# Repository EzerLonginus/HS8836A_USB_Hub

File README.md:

# HS8836A_USB_Hub
Simple usb 2.0 hub using the HS8836A.  There are two designs, one is designed specifically for mounting directly to the side of my laptop, the other is with USB-C or USB Mini connectors and probably the one you'll want to actually look at..  
This schematic is identical to [Stefan Wagner](https://github.com/wagiminator) schematic at [OSHW Lab](https://oshwlab.com/wagiminator/hs8836-usb-2-0-hub_copy)

## Purpose
Originally, and more importantly for me, I wanted to design a slim-ish USB hub that I could connect to the side of my computer, without a cable dangling from it.  The design also needed to allow for airflow from the fans that are next to the USB port on my computer, and not to obstruct the other ports on the other side of the USB.  That being said, I created an addtional design to be a little more universally applicable for others (and myself later).  So likely you'll want to use the [HSS8836_USBC_Hub](hardware/HS8836A_USBC_hub) files instead of the older ones.  The older files are still available, although it's probably not really needed for anyone besides me.

## Scematic

## Layout

## To Do
* Post pictures of the old USB hub
* Populate and Test USBC Hub when boards arrive
* Post pictures of USBC board

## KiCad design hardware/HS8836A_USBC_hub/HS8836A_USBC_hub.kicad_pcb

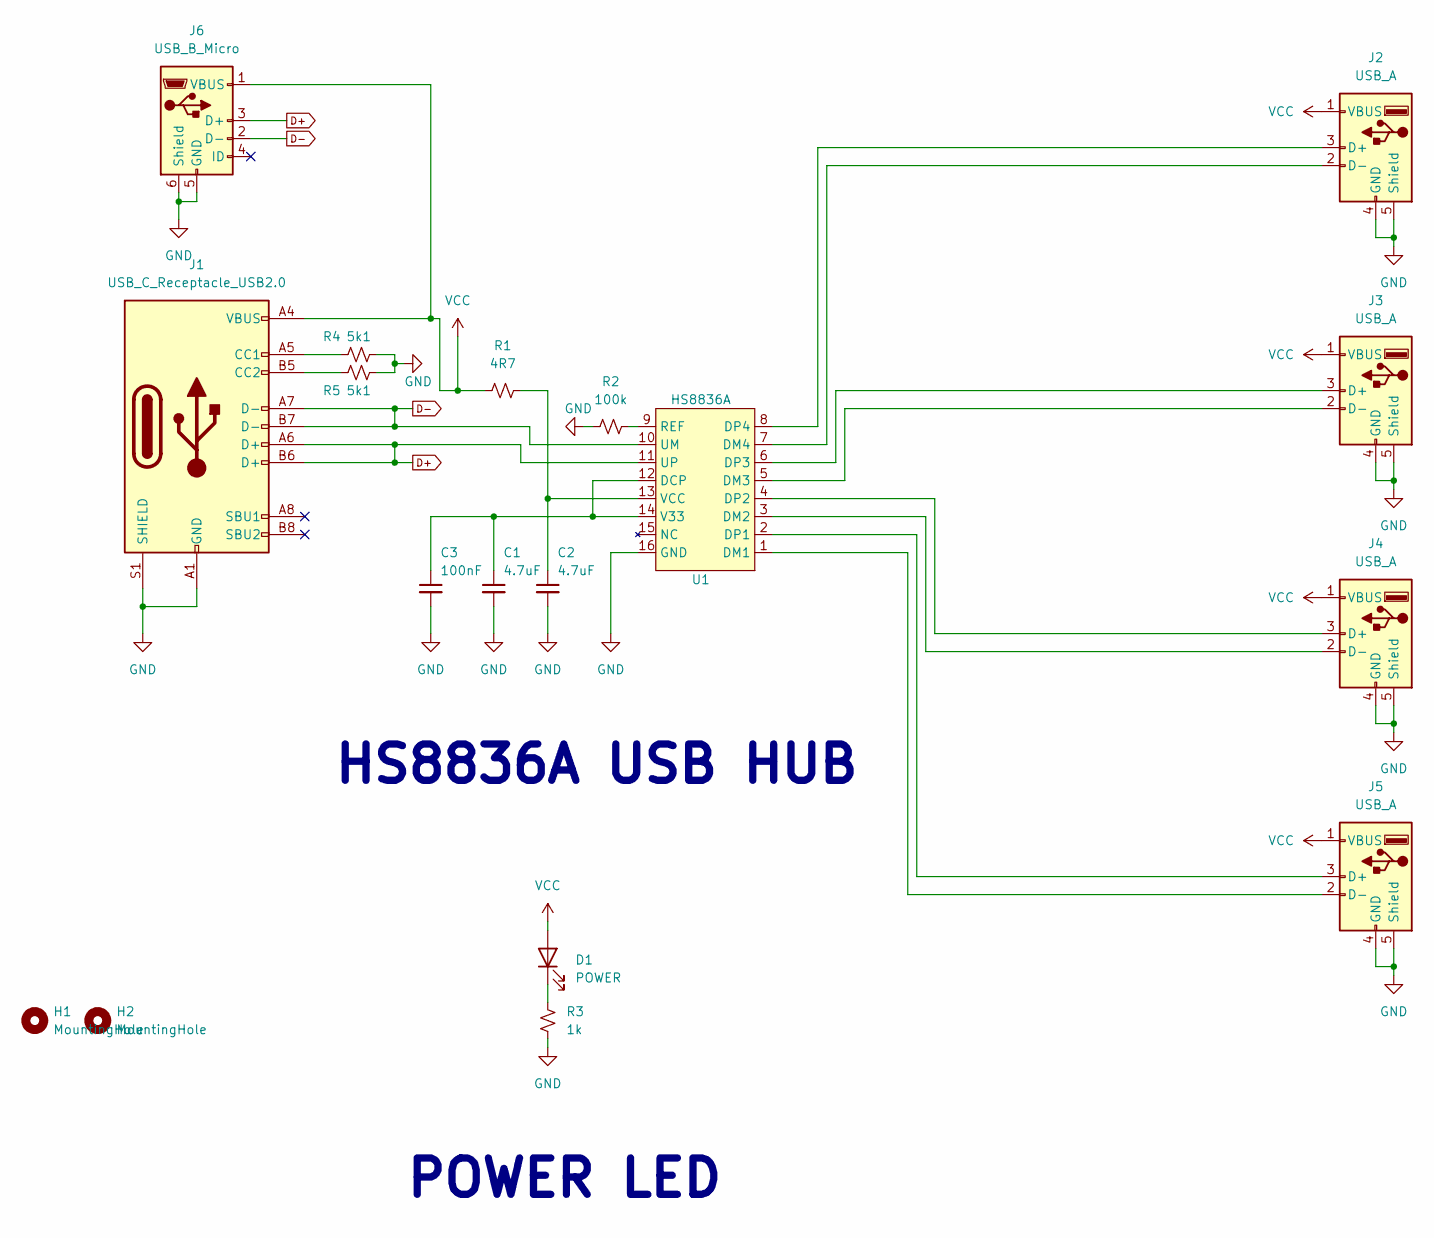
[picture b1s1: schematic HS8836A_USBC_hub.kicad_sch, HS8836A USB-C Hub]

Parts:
C1, C2: 4.7uF; C_0603_1608Metric_Pad1.08x0.95mm_HandSolder
C3: 100nF; C_0603_1608Metric_Pad1.08x0.95mm_HandSolder
D1: POWER; LED_1206_3216Metric
H1, H2: MountingHole; MountingHole_2.2mm_M2
J1: USB_C_Receptacle_USB2.0; USB_C_Receptacle_HRO_TYPE-C-31-M-12
J2, J3, J4, J5: USB_A; USB_A_Molex_67643_Horizontal
J6: USB_B_Micro; USB_Micro-B_Amphenol_10118193-0001LF_Horizontal
R1: 4R7; R_0603_1608Metric_Pad0.98x0.95mm_HandSolder
R2: 100k; R_0603_1608Metric_Pad0.98x0.95mm_HandSolder
R3: 1k; R_0603_1608Metric_Pad0.98x0.95mm_HandSolder
R4, R5: 5k1; R_0603_1608Metric_Pad0.98x0.95mm_HandSolder
U1: HS8836A; SOP-16_4.4x10.4mm_P1.27mm

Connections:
D+: J1.A6 (D+), J1.B6 (D+), J6.3 (D+), U1.11 (UP)
D-: J1.A7 (D-), J1.B7 (D-), J6.2 (D-), U1.10 (UM)
GND: C1.2, C2.2, C3.2, J1.A1 (GND), J1.A12 (GND), J1.B1 (GND), J1.B12 (GND), J1.S1 (SHIELD), J2.4 (GND), J2.5 (Shield), J3.4 (GND), J3.5 (Shield), J4.4 (GND), J4.5 (Shield), J5.4 (GND), J5.5 (Shield), J6.5 (GND), J6.6 (Shield), R2.1, R3.1, R4.2, R5.2, U1.16 (GND)
unnamed: D1.1 (K), R3.2
unnamed: J1.A5 (CC1), R4.1
unnamed: J1.B5 (CC2), R5.1
unnamed: J2.3 (D+), U1.8 (DP4)
unnamed: J2.2 (D-), U1.7 (DM4)
unnamed: J3.3 (D+), U1.6 (DP3)
unnamed: J3.2 (D-), U1.5 (DM3)
unnamed: J4.3 (D+), U1.4 (DP2)
unnamed: J4.2 (D-), U1.3 (DM2)
unnamed: J5.3 (D+), U1.2 (DP1)
unnamed: J5.2 (D-), U1.1 (DM1)
unnamed: C1.1, C3.1, U1.12 (DCP), U1.14 (V33)
unnamed: R2.2, U1.9 (REF)
unnamed: C2.1, R1.2, U1.13 (VCC)
VCC: D1.2 (A), J1.A4 (VBUS), J1.A9 (VBUS), J1.B4 (VBUS), J1.B9 (VBUS), J2.1 (VBUS), J3.1 (VBUS), J4.1 (VBUS), J5.1 (VBUS), J6.1 (VBUS), R1.1

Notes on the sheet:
HS8836A USB HUB
POWER LED

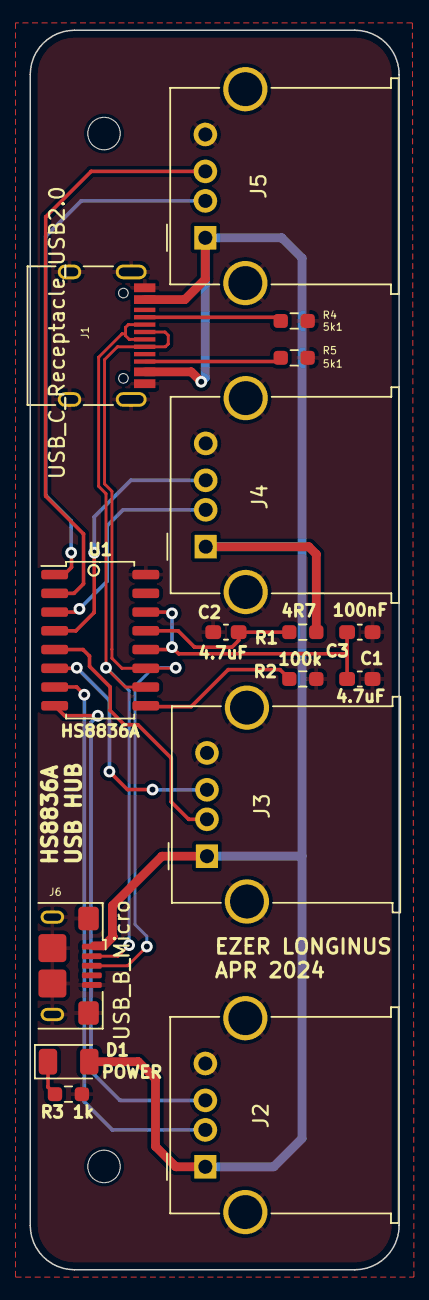
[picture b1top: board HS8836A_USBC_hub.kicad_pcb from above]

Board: 2 copper layers, 25.0 x 84.0 mm, 18 parts (0 on the bottom side), 18 nets.

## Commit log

2024-02-11 Initial Design Commit
2024-03-19 Made the USB hub a little more universally applicable
2024-04-05 swapped dp and dm lines on the controller
2024-04-13 Updated Gerbers and images
